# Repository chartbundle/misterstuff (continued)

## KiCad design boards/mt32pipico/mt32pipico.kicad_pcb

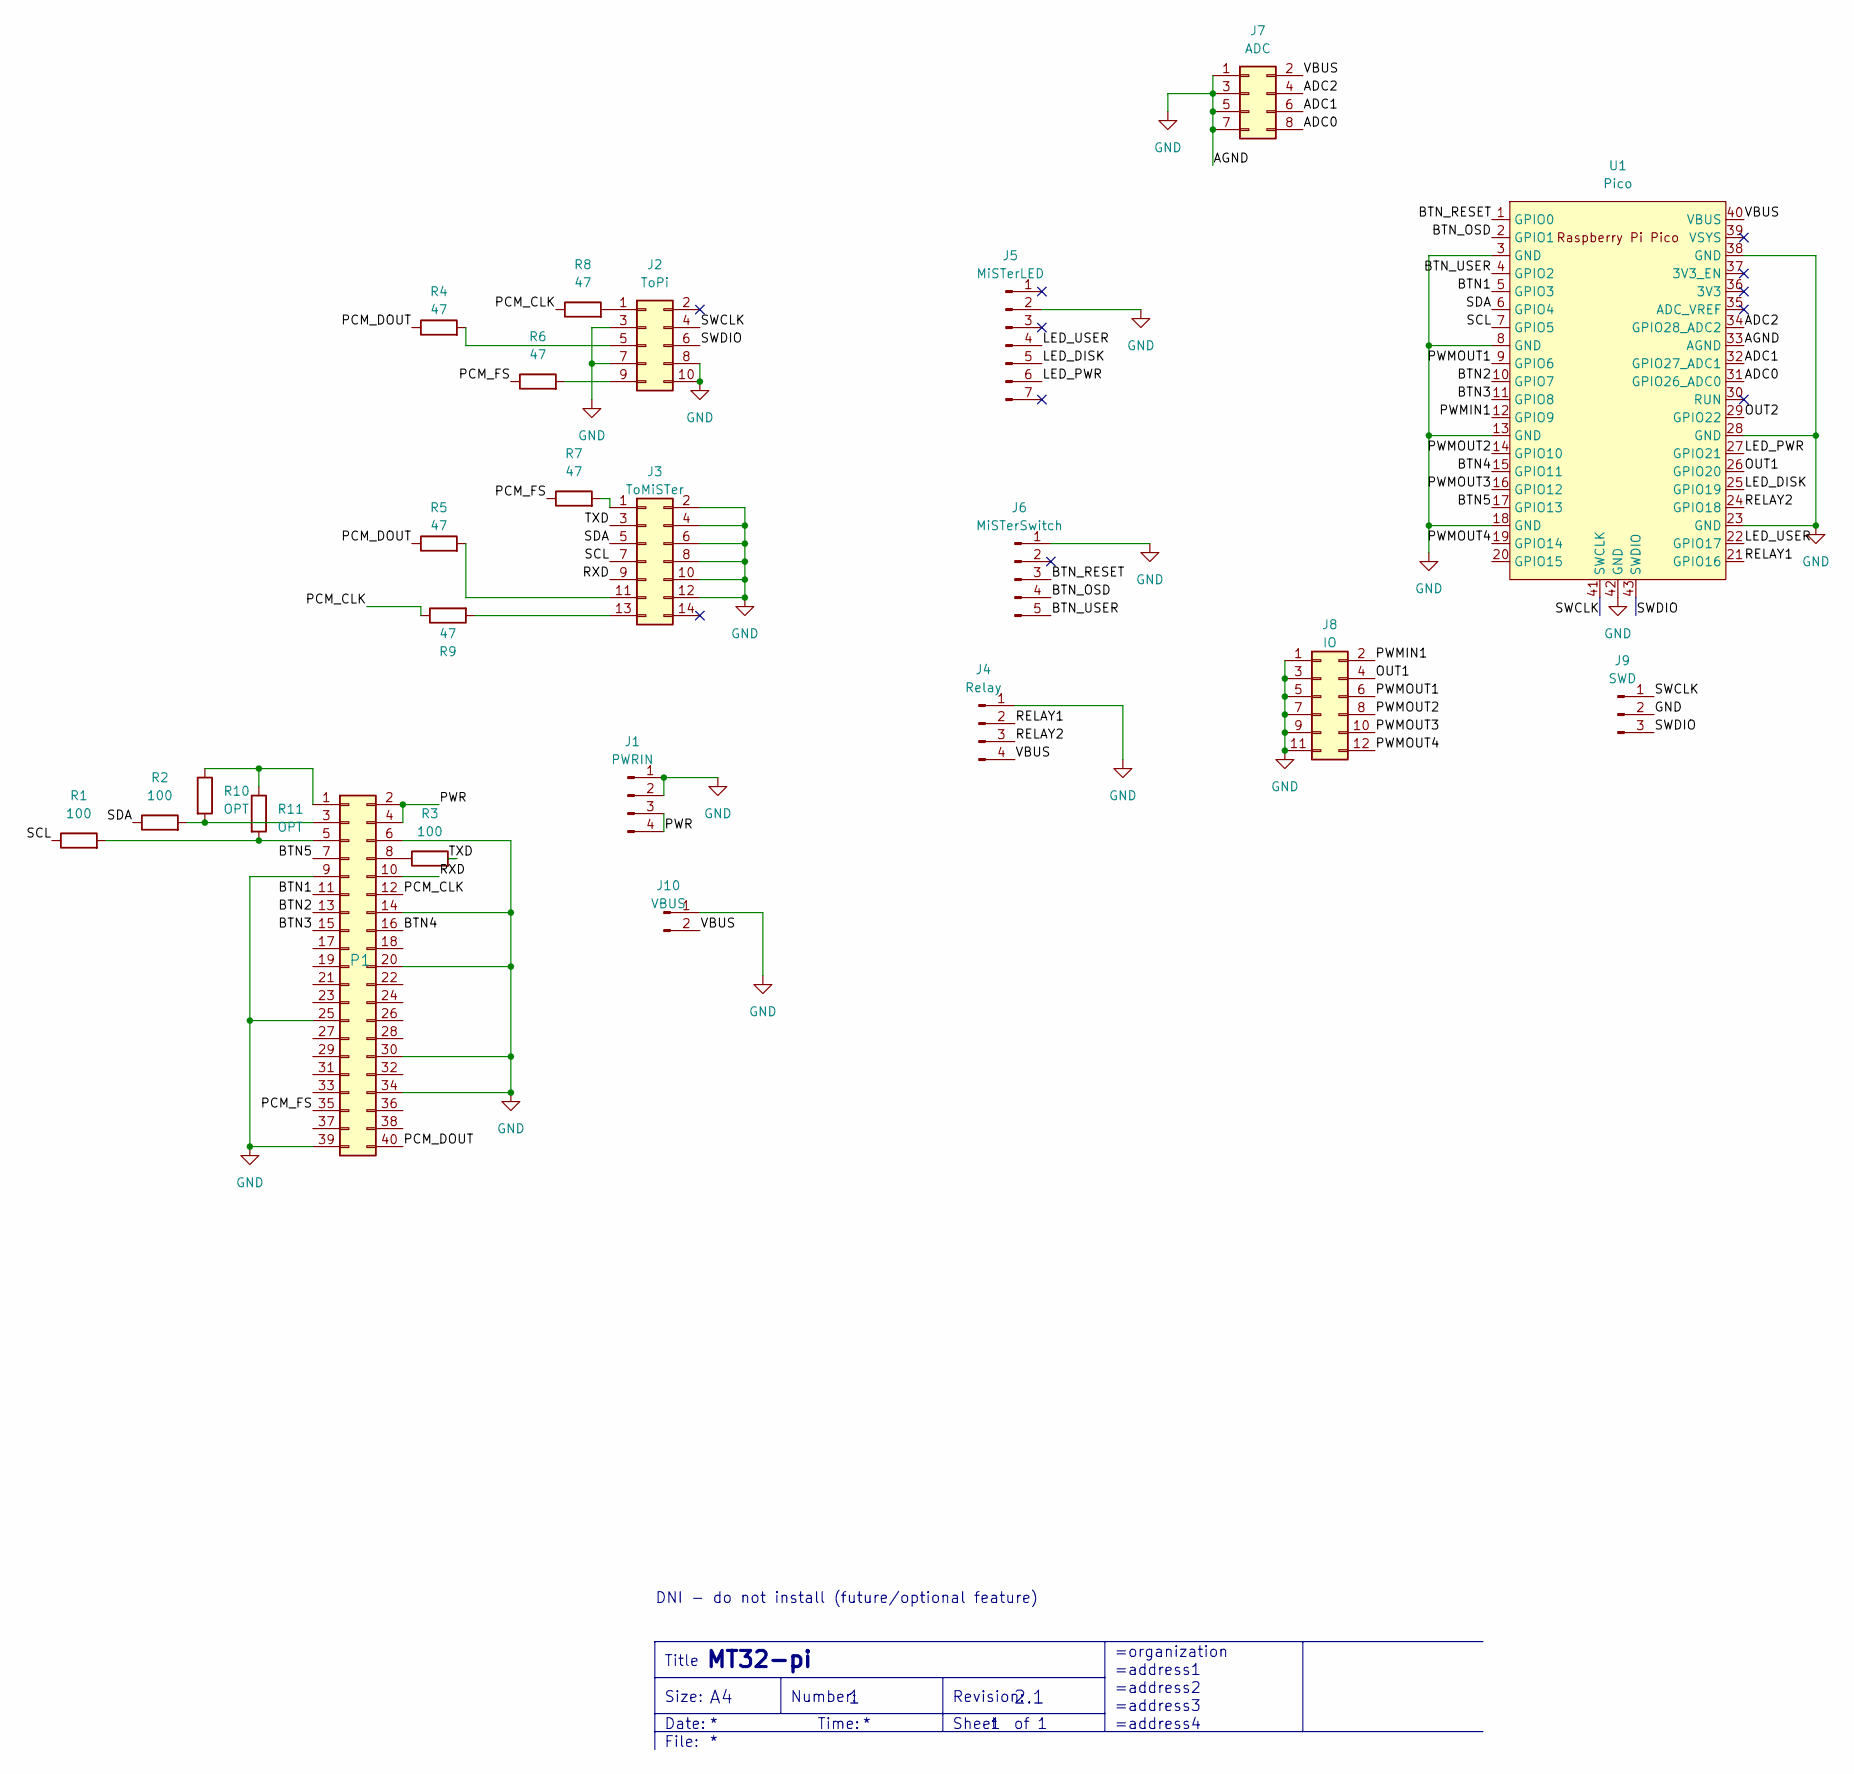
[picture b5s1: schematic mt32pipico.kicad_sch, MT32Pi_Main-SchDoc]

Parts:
J1: PWRIN; PinHeader_1x04_P2.54mm_Vertical
J2: ToPi; PinHeader_2x05_P2.54mm_Vertical
J3: ToMiSTer; PinHeader_2x07_P2.54mm_Vertical
J4: Relay; PinHeader_1x04_P2.54mm_Vertical
J5: MiSTerLED; JST_XH_B7B-XH-A_1x07_P2.50mm_Vertical
J6: MiSTerSwitch; JST_XH_B5B-XH-A_1x05_P2.50mm_Vertical
J7: ADC; PinHeader_2x04_P2.54mm_Vertical
J8: IO; PinHeader_2x06_P2.54mm_Vertical
J9: SWD; PinHeader_1x03_P2.54mm_Vertical
J10: VBUS; PinHeader_1x02_P2.54mm_Vertical
P1: PinHeader_2x20_P2.54mm_Vertical
R1, R2, R3: 100; R_0805_2012Metric
R4, R5, R6, R7, R8, R9: 47; R_0805_2012Metric
R10, R11: OPT; R_0805_2012Metric
U1: Pico; RPi_Pico_SMD_TH

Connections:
/ADC0: J7.8, U1.31 (GPIO26_ADC0)
/ADC1: J7.6, U1.32 (GPIO27_ADC1)
/ADC2: J7.4, U1.34 (GPIO28_ADC2)
/BTN1: P1.11, U1.5 (GPIO3)
/BTN2: P1.13, U1.10 (GPIO7)
/BTN3: P1.15, U1.11 (GPIO8)
/BTN4: P1.16, U1.15 (GPIO11)
/BTN5: P1.7, U1.17 (GPIO13)
/BTN_OSD: J6.4, U1.2 (GPIO1)
/BTN_RESET: J6.3, U1.1 (GPIO0)
/BTN_USER: J6.5, U1.4 (GPIO2)
/LED_DISK: J5.5, U1.25 (GPIO19)
/LED_PWR: J5.6, U1.27 (GPIO21)
/LED_USER: J5.4, U1.22 (GPIO17)
/OUT1: J8.4, U1.26 (GPIO20)
/OUT2: U1.29 (GPIO22)
/PCM_CLK: P1.12, R8.1, R9.1
/PCM_DOUT: P1.40, R4.1, R5.1
/PCM_FS: P1.35, R6.1, R7.1
/PWMIN1: J8.2, U1.12 (GPIO9)
/PWMOUT1: J8.6, U1.9 (GPIO6)
/PWMOUT2: J8.8, U1.14 (GPIO10)
/PWMOUT3: J8.10, U1.16 (GPIO12)
/PWMOUT4: J8.12, U1.19 (GPIO14)
/PWR: J1.3, J1.4, P1.2, P1.4
/RELAY1: J4.2, U1.21 (GPIO16)
/RELAY2: J4.3, U1.24 (GPIO18)
/RXD: J3.9, P1.10
/SCL: J3.7, R1.1, U1.7 (GPIO5)
/SDA: J3.5, R2.1, U1.6 (GPIO4)
/SWCLK: J2.4, J9.1, U1.41 (SWCLK)
/SWDIO: J2.6, J9.3, U1.43 (SWDIO)
/TXD: J3.3, R3.2
/VBUS: J4.4, J7.2, J10.2, U1.40 (VBUS)
GND: J1.1, J1.2, J2.3, J2.7, J2.8, J2.10, J3.2, J3.4, J3.6, J3.8, J3.10, J3.12, J4.1, J5.2, J6.1, J7.1, J7.3, J7.5, J7.7, J8.1, J8.3, J8.5, J8.7, J8.9, J8.11, J9.2, J10.1, P1.6, P1.9, P1.14, P1.20, P1.25, P1.30, P1.34, P1.39, U1.3 (GND), U1.8 (GND), U1.13 (GND), U1.18 (GND), U1.23 (GND), U1.28 (GND), U1.33 (AGND), U1.38 (GND), U1.42 (GND)
unnamed: J2.1, R8.2
unnamed: J2.5, R4.2
unnamed: J2.9, R6.2
unnamed: J3.1, R7.2
unnamed: J3.11, R5.2
unnamed: J3.13, R9.2
unnamed: P1.1, R10.1, R11.1
unnamed: P1.3, R2.2, R10.2
unnamed: P1.5, R1.2, R11.2
unnamed: P1.8, R3.1

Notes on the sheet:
Title
=address3
Date:
=organization
Revision:
=address1
MT32-pi
Number:
=address2
Time:
Sheet
File:
=address4
Size:
DNI - do not install (future/optional feature)
2.1

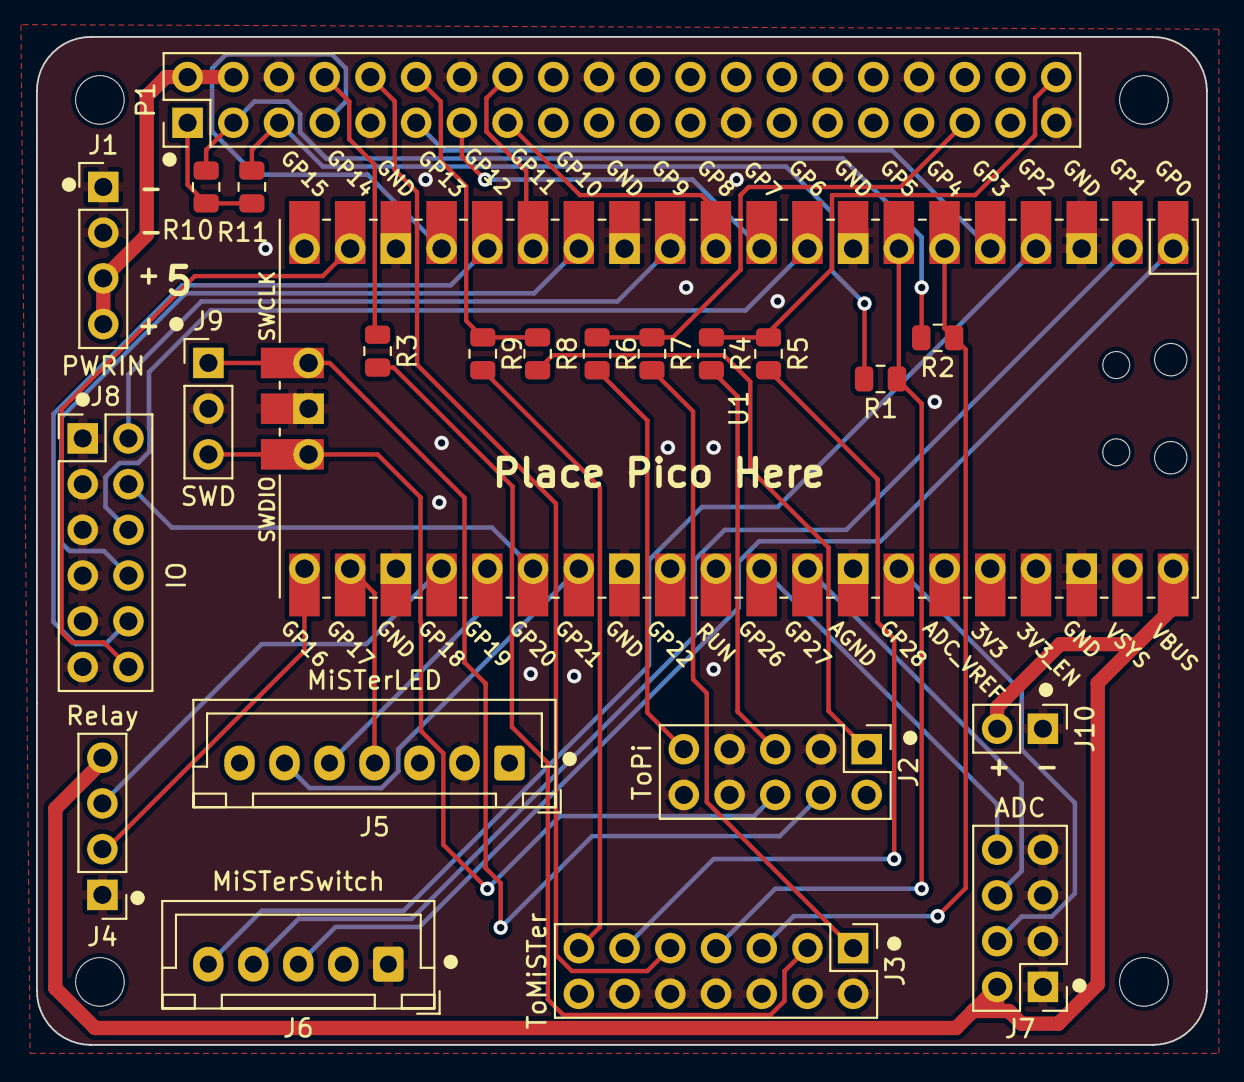
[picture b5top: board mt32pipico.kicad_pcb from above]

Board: 2 copper layers, 65.0 x 56.0 mm, 27 parts (0 on the bottom side), 44 nets.

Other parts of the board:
MH1, MH2, MH3, MH4: MountingHole_2.7mm_M2.5

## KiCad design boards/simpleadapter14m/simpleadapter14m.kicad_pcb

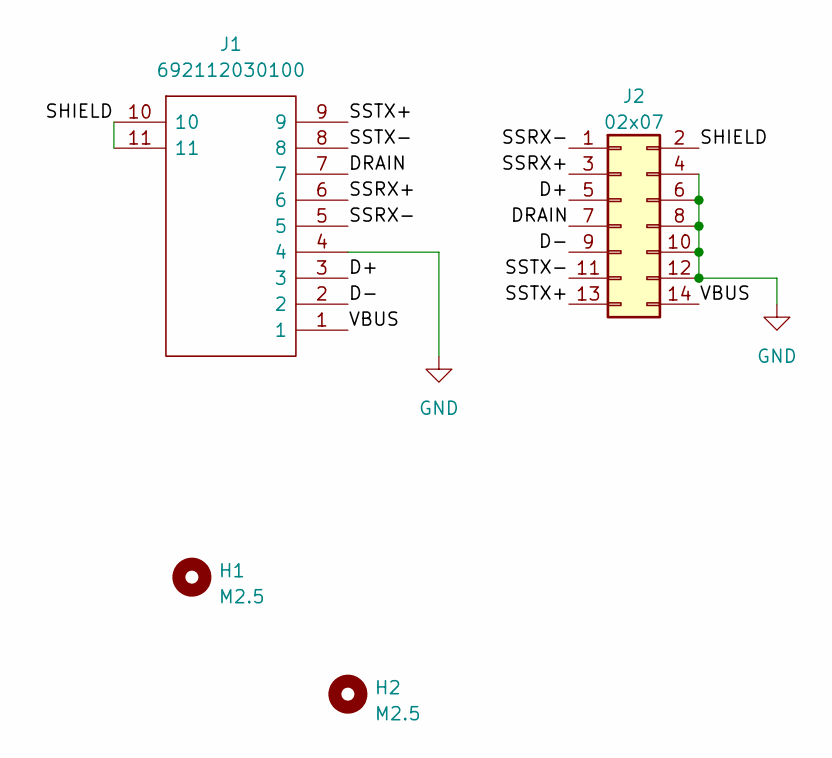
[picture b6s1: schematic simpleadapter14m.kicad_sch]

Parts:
H1, H2: M2.5; MountingHole_2.7mm_M2.5
J1: 692112030100; Mouser2 Part Number 710-692112030100
J2: 02x07; PinHeader_2x07_P2.54mm_Vertical

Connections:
/D+: J1.3, J2.5
/D-: J1.2, J2.9
/DRAIN: J1.7, J2.7
/SHIELD: J1.10, J1.11, J2.2
/SSRX+: J1.6, J2.3
/SSRX-: J1.5, J2.1
/SSTX+: J1.9, J2.13
/SSTX-: J1.8, J2.11
/VBUS: J1.1, J2.14
GND: J1.4, J2.4, J2.6, J2.8, J2.10, J2.12

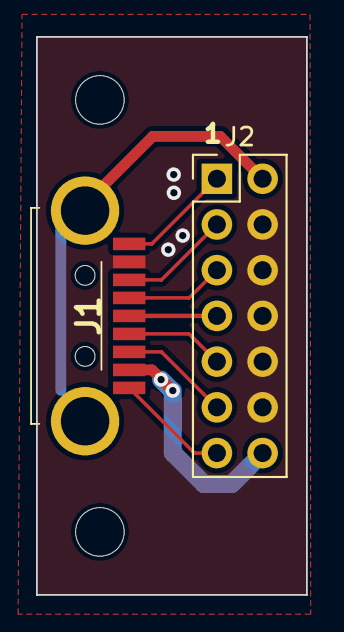
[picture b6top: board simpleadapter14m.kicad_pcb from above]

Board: 2 copper layers, 15.0 x 31.0 mm, 4 parts (0 on the bottom side), 10 nets.

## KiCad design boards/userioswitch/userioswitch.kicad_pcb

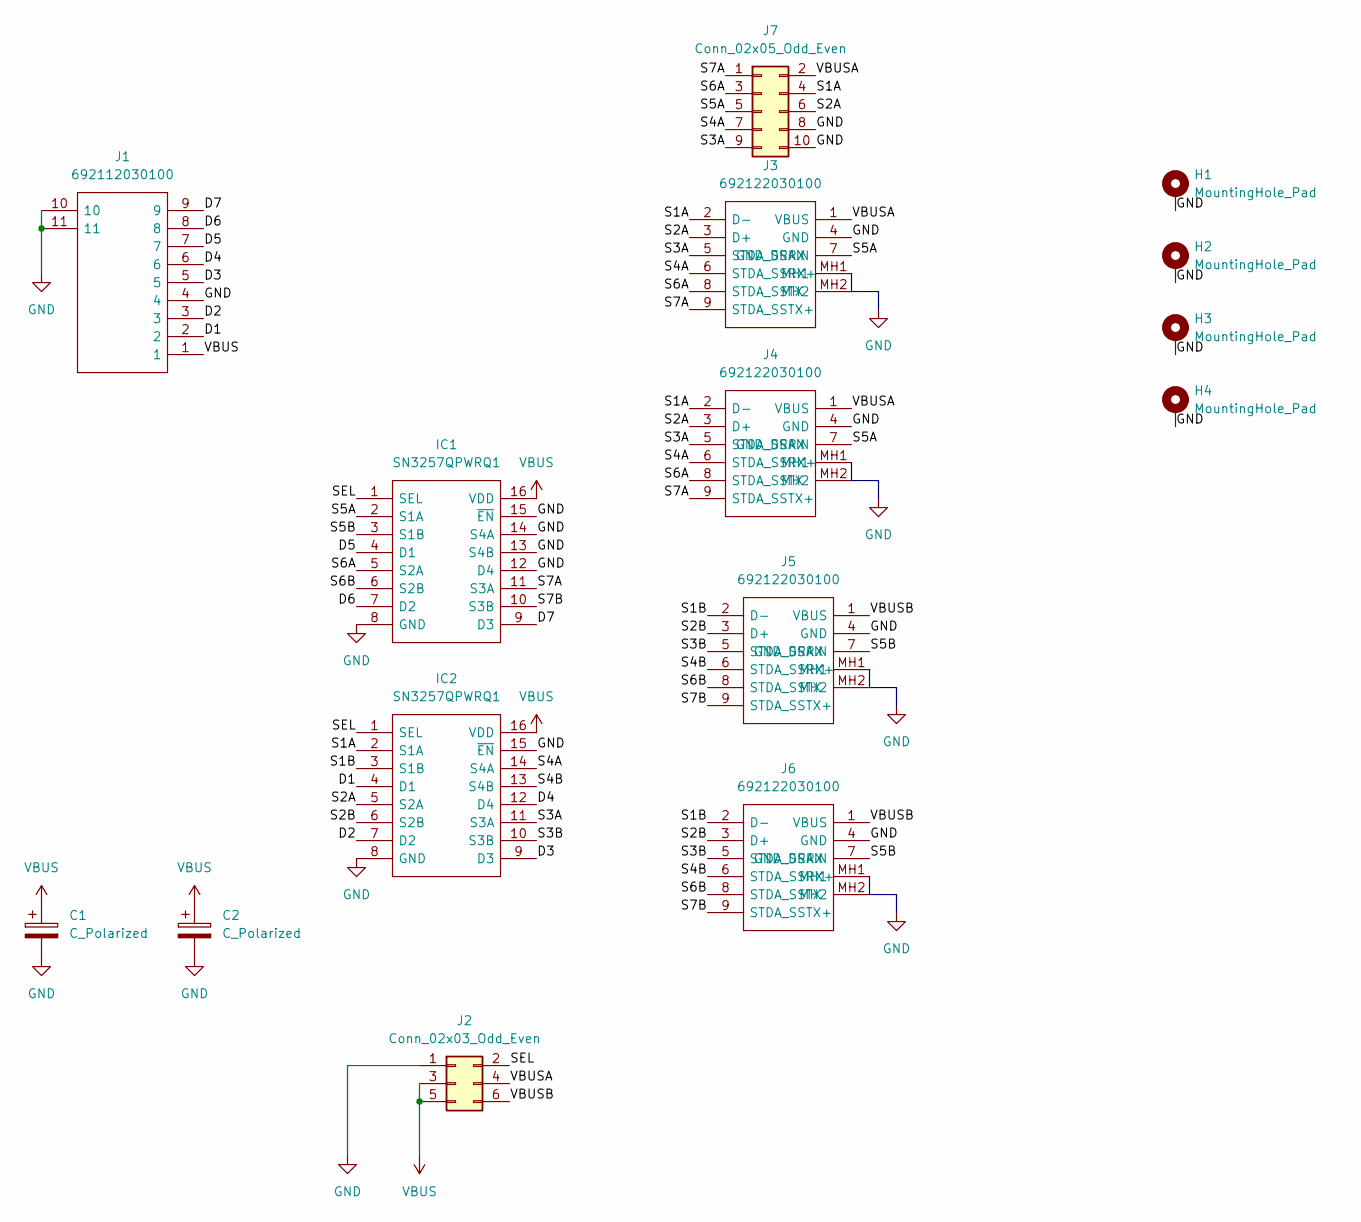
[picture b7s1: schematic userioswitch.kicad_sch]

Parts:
C1, C2: C_Polarized; C_0805_2012Metric
H1, H2, H3, H4: MountingHole_Pad; MountingHole_3.2mm_M3_Pad_TopBottom
IC1, IC2: SN3257QPWRQ1; SOP65P640X120-16N; Manufacturer_Part_Number SN3257QPWRQ1
J1: 692112030100; 692112030100-fixed; Mouser2 Part Number 710-692112030100
J2: Conn_02x03_Odd_Even; PinHeader_2x03_P2.54mm_Vertical
J3, J4, J5, J6: 692122030100; Mouser2 Part Number 710-692122030100
J7: Conn_02x05_Odd_Even; PinHeader_2x05_P2.54mm_Vertical

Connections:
/D1: IC2.4 (D1), J1.2
/D2: IC2.7 (D2), J1.3
/D3: IC2.9 (D3), J1.5
/D4: IC2.12 (D4), J1.6
/D5: IC1.4 (D1), J1.7
/D6: IC1.7 (D2), J1.8
/D7: IC1.9 (D3), J1.9
/S1A: IC2.2 (S1A), J3.2 (D-), J4.2 (D-), J7.4
/S1B: IC2.3 (S1B), J5.2 (D-), J6.2 (D-)
/S2A: IC2.5 (S2A), J3.3 (D+), J4.3 (D+), J7.6
/S2B: IC2.6 (S2B), J5.3 (D+), J6.3 (D+)
/S3A: IC2.11 (S3A), J3.5 (STDA_SSRX), J4.5 (STDA_SSRX), J7.9
/S3B: IC2.10 (S3B), J5.5 (STDA_SSRX), J6.5 (STDA_SSRX)
/S4A: IC2.14 (S4A), J3.6 (STDA_SSRX+), J4.6 (STDA_SSRX+), J7.7
/S4B: IC2.13 (S4B), J5.6 (STDA_SSRX+), J6.6 (STDA_SSRX+)
/S5A: IC1.2 (S1A), J3.7 (GND_DRAIN), J4.7 (GND_DRAIN), J7.5
/S5B: IC1.3 (S1B), J5.7 (GND_DRAIN), J6.7 (GND_DRAIN)
/S6A: IC1.5 (S2A), J3.8 (STDA_SSTX), J4.8 (STDA_SSTX), J7.3
/S6B: IC1.6 (S2B), J5.8 (STDA_SSTX), J6.8 (STDA_SSTX)
/S7A: IC1.11 (S3A), J3.9 (STDA_SSTX+), J4.9 (STDA_SSTX+), J7.1
/S7B: IC1.10 (S3B), J5.9 (STDA_SSTX+), J6.9 (STDA_SSTX+)
/SEL: IC1.1 (SEL), IC2.1 (SEL), J2.2; also elsewhere on the board
/VBUSA: J2.4, J3.1 (VBUS), J4.1 (VBUS), J7.2
/VBUSB: J2.6, J5.1 (VBUS), J6.1 (VBUS)
GND: C1.2, C2.2, H1.1, H2.1, H3.1, H4.1, IC1.8 (GND), IC1.12 (D4), IC1.13 (S4B), IC1.14 (S4A), IC1.15 (~EN), IC2.8 (GND), IC2.15 (~EN), J1.4, J1.10, J1.11, J2.1, J3.4 (GND), J3.MH1, J3.MH2, J4.4 (GND), J4.MH1, J4.MH2, J5.4 (GND), J5.MH1, J5.MH2, J6.4 (GND), J6.MH1, J6.MH2, J7.8, J7.10
VBUS: C1.1, C2.1, IC1.16 (VDD), IC2.16 (VDD), J1.1, J2.3, J2.5; also elsewhere on the board

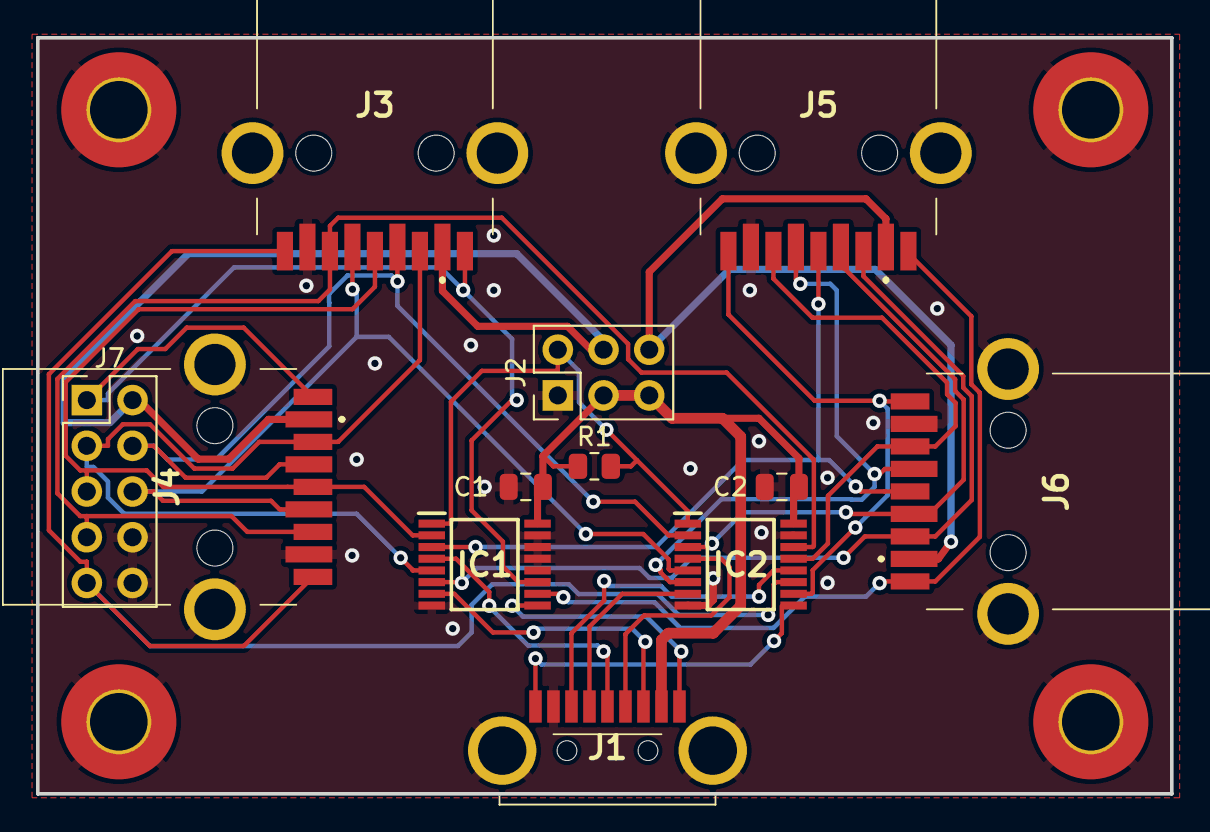
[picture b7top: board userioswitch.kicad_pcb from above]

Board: 2 copper layers, 63.0 x 42.0 mm, 16 parts (0 on the bottom side), 26 nets.

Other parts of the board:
R1: 4K7; R_0805_2012Metric

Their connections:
/SEL: R1.2; also elsewhere on the board
VBUS: R1.1; also elsewhere on the board

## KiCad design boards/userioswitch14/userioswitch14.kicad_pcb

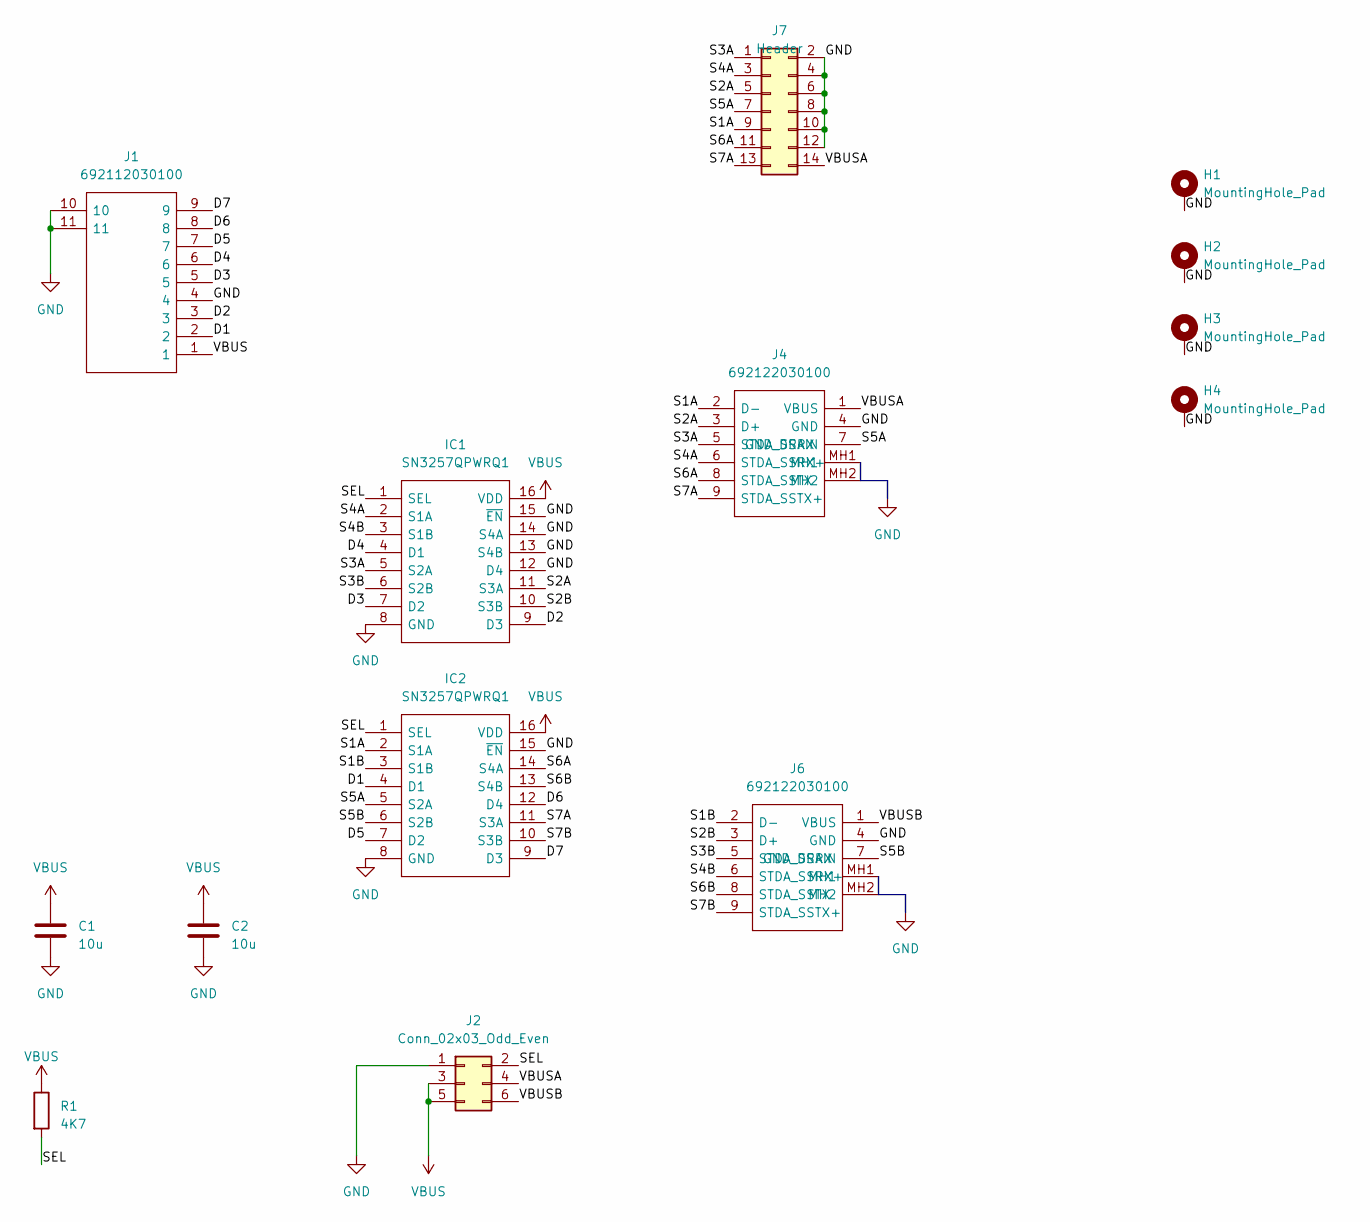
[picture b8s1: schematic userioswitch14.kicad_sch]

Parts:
C1, C2: 10u; C_0805_2012Metric
H1, H2, H3, H4: MountingHole_Pad; MountingHole_3.2mm_M3_Pad_TopBottom
IC1, IC2: SN3257QPWRQ1; SOP65P640X120-16N; Manufacturer_Part_Number SN3257QPWRQ1
J1: 692112030100; 692112030100-fixed; Mouser2 Part Number 710-692112030100
J2: Conn_02x03_Odd_Even; PinHeader_2x03_P2.54mm_Vertical
J4, J6: 692122030100; Mouser2 Part Number 710-692122030100
J7: Header; PinHeader_2x07_P2.54mm_Vertical
R1: 4K7; R_0805_2012Metric

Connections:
/D1: IC2.4 (D1), J1.2
/D2: IC1.9 (D3), J1.3
/D3: IC1.7 (D2), J1.5
/D4: IC1.4 (D1), J1.6
/D5: IC2.7 (D2), J1.7
/D6: IC2.12 (D4), J1.8
/D7: IC2.9 (D3), J1.9
/S1A: IC2.2 (S1A), J4.2 (D-), J7.9
/S1B: IC2.3 (S1B), J6.2 (D-)
/S2A: IC1.11 (S3A), J4.3 (D+), J7.5
/S2B: IC1.10 (S3B), J6.3 (D+)
/S3A: IC1.5 (S2A), J4.5 (STDA_SSRX), J7.1
/S3B: IC1.6 (S2B), J6.5 (STDA_SSRX)
/S4A: IC1.2 (S1A), J4.6 (STDA_SSRX+), J7.3
/S4B: IC1.3 (S1B), J6.6 (STDA_SSRX+)
/S5A: IC2.5 (S2A), J4.7 (GND_DRAIN), J7.7
/S5B: IC2.6 (S2B), J6.7 (GND_DRAIN)
/S6A: IC2.14 (S4A), J4.8 (STDA_SSTX), J7.11
/S6B: IC2.13 (S4B), J6.8 (STDA_SSTX)
/S7A: IC2.11 (S3A), J4.9 (STDA_SSTX+), J7.13
/S7B: IC2.10 (S3B), J6.9 (STDA_SSTX+)
/SEL: IC1.1 (SEL), IC2.1 (SEL), J2.2, R1.2
/VBUSA: J2.4, J4.1 (VBUS), J7.14
/VBUSB: J2.6, J6.1 (VBUS)
GND: C1.2, C2.2, H1.1, H2.1, H3.1, H4.1, IC1.8 (GND), IC1.12 (D4), IC1.13 (S4B), IC1.14 (S4A), IC1.15 (~EN), IC2.8 (GND), IC2.15 (~EN), J1.4, J1.10, J1.11, J2.1, J4.4 (GND), J4.MH1, J4.MH2, J6.4 (GND), J6.MH1, J6.MH2, J7.2, J7.4, J7.6, J7.8, J7.10, J7.12
VBUS: C1.1, C2.1, IC1.16 (VDD), IC2.16 (VDD), J1.1, J2.3, J2.5, R1.1

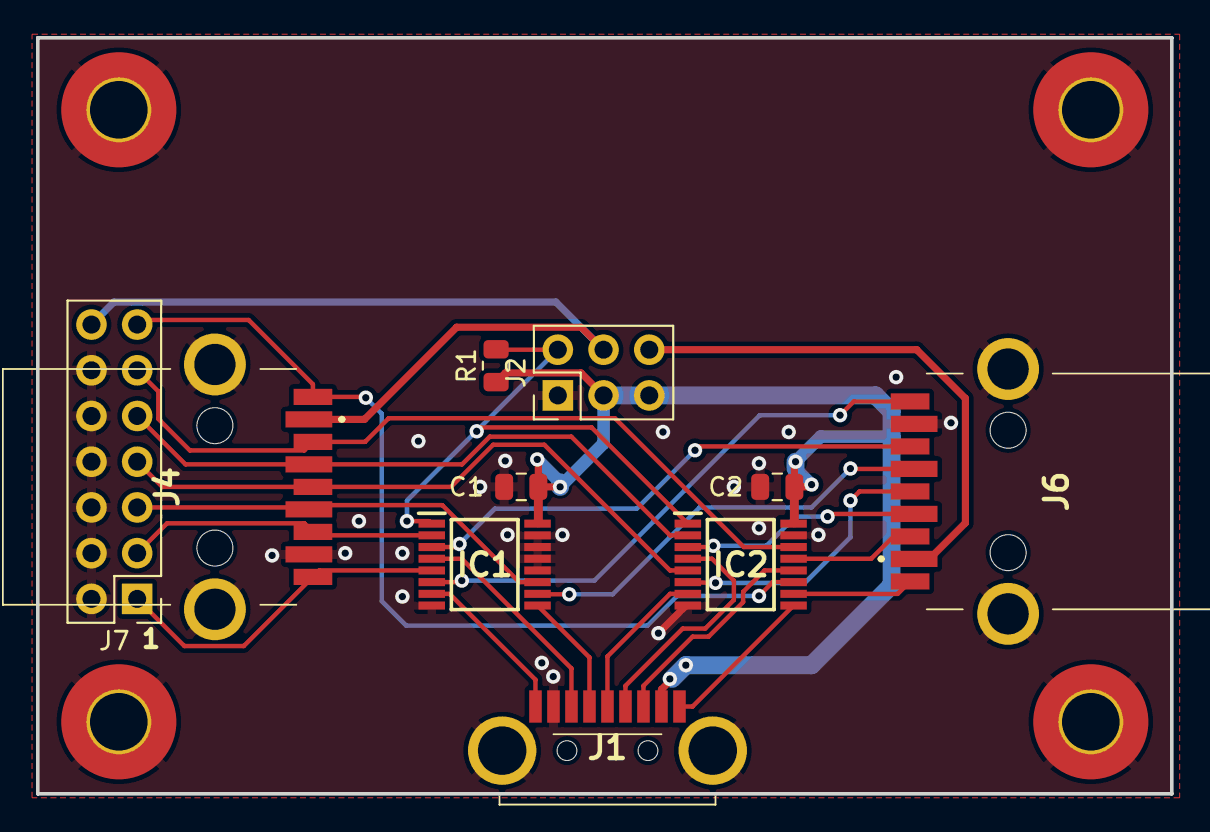
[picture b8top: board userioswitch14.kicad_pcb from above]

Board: 2 copper layers, 63.0 x 42.0 mm, 14 parts (0 on the bottom side), 26 nets.

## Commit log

2023-02-28 Schematic_and_pcb
2023-03-01 MisterPico
2023-03-01 Stop checking in the build directory
2023-03-01 Now with the UDP code
2023-03-01 Add TinyUSB Submodule
2023-03-01 Remove submodule, should be in SDK
2023-03-07 more comments
2023-03-12 Move to 14 pin headers for switch with off-board adapters
2023-03-17 More ignore
2023-03-17 Track stuff
2023-03-20 Add stuff
2023-03-20 Move older 10 pin connections out of the way
2023-03-20 Cleanup
2023-03-20 Remove Autorouter files
2023-03-20 Add schematic and pcb
2023-03-20 Add Readme
2023-04-05 Pending updates
2023-04-05 Add Photo
2025-03-10 Remove float, make the receiver do it
2025-03-10 Add binary output for ADC
2025-03-10 Branch to make updates to TinyUSB, LWIP, and Pico SDKx
2025-08-10 Clean up gerbers, checkpoint pico code
2025-08-17 Oopdates
2025-10-14 backups
